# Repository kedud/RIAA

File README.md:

# RIAA

This module is a switchable RIAA/Line preamp for RM4 mixer project.

Some of the part are not present on the schematic:
 - Molex crimps

| Parts 			| 	 Part ref		|
| ----------------- | ----------------- |
| Molex crimps 		| 538-08-50-0114    |

The BoM for this schematics can be found [here](https://octopart.com/bom-tool/uFlDQjD4)

A Mouser cart is also available [here](https://www.mouser.com/ProjectManager/ProjectDetail.aspx?AccessID=9f5cd040c6)

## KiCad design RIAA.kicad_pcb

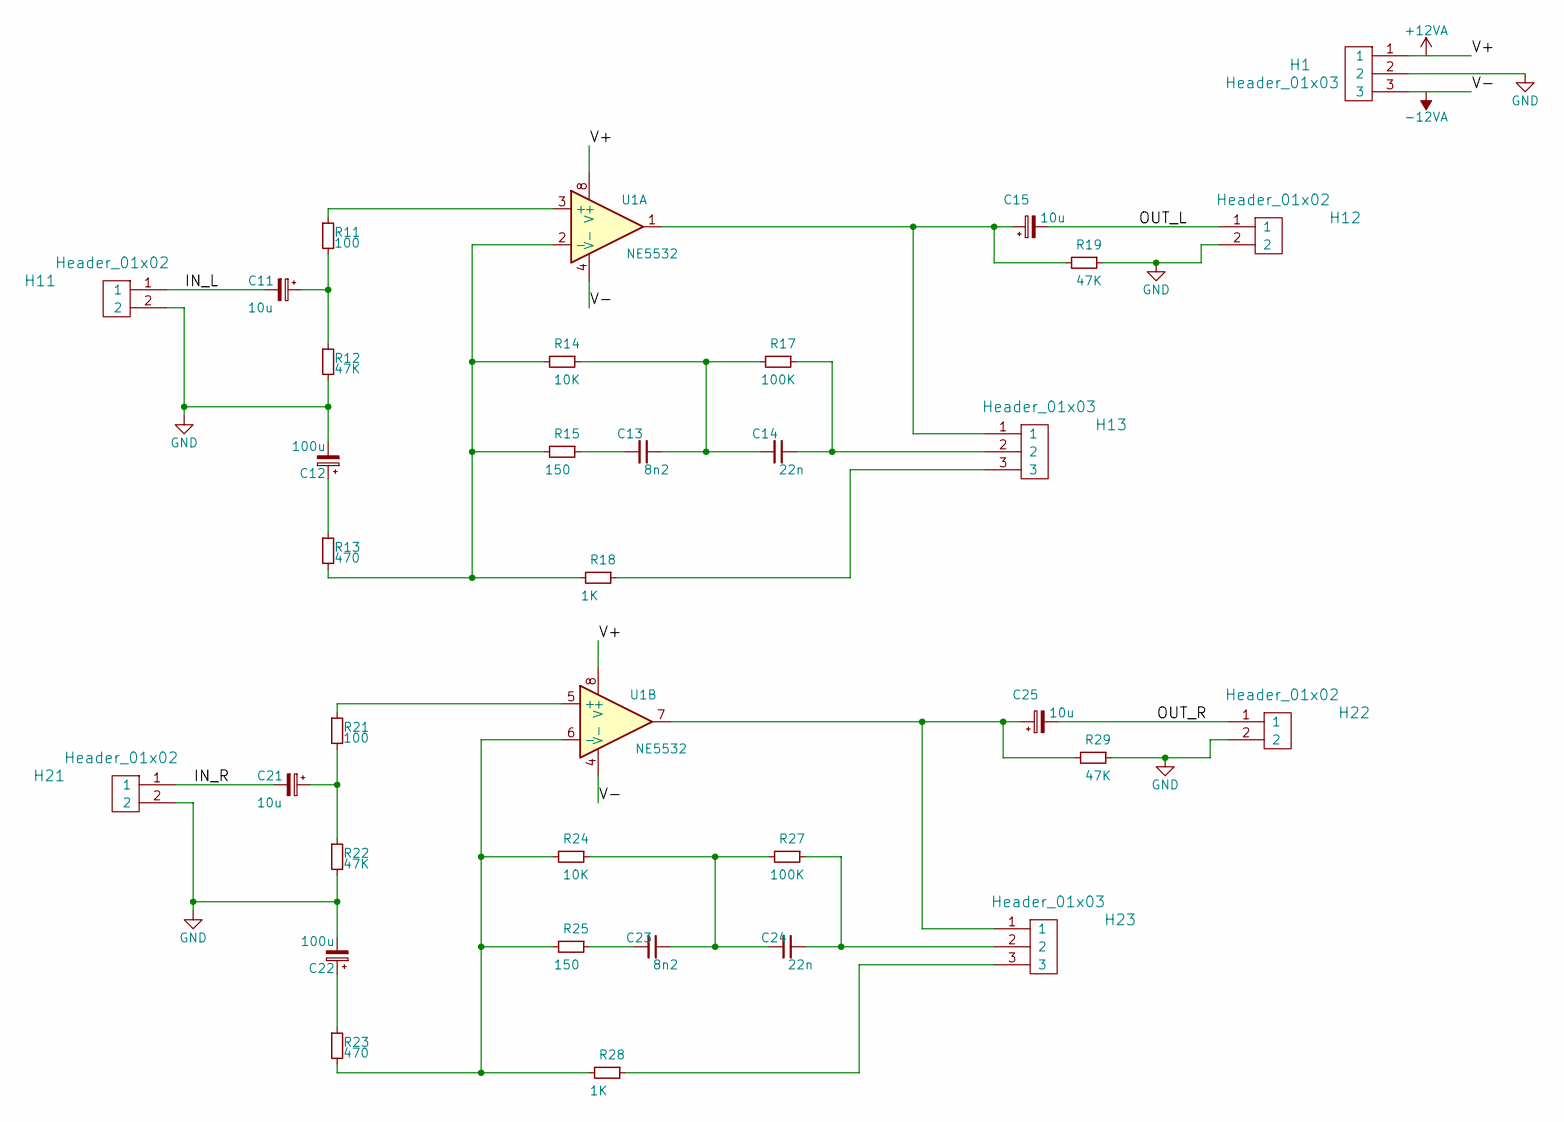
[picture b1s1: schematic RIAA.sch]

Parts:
C11, C21: 10u; C_Radial_D5_L11_P2.5; Mfg_Part_No UVR1V100MDD1TA
C12, C22: 100u; C_Radial_D5_L11_P2.5; Mfg_Part_No UVR1A101MDD
C13, C23: 8n2; C_Rect_L7_W2.5_P5; Mfg_Part_No QYX2A822KTP
C14, C24: 22n; C_Rect_L7_W2.5_P5; Mfg_Part_No QYX2A223KTP
C15, C25: 10u; C_Radial_D5_L11_P2.5; Mfg_Part_No UVR1A101MDD
H1, H13, H23: Header_01x03; Pin_Header_Straight_1x03
H11, H12, H21, H22: Header_01x02; Pin_Header_Straight_1x02
R11, R21: 100; Resistor_Horizontal_RM10mm; Mfg_Part_No CCF07100RJKE36
R12, R19, R22, R29: 47K; Resistor_Horizontal_RM10mm; Mfg_Part_No CCF0747K0GKE36
R13, R23: 470; Resistor_Horizontal_RM10mm; Mfg_Part_No CCF07470RGKE36 CCF07470RGKE36 CCF07470R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
R14, R24: 10K; Resistor_Horizontal_RM10mm; Mfg_Part_No CCF0710K0GKE36
R15, R25: 150; Resistor_Horizontal_RM10mm; Mfg_Part_No CCF07150RGKE36
R17, R27: 100K; Resistor_Horizontal_RM10mm; Mfg_Part_No CCF07100KGKE36
R18, R28: 1K; Resistor_Horizontal_RM10mm
U1: NE5532; DIP-8_W7.62mm_LongPads; Mfg_Part_No NE5532P

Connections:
/IN_L: C11.2, H11.1
/IN_R: C21.2, H21.1
/OUT_L: C15.2, H12.1
/OUT_R: C25.2, H22.1
/V+: H1.1, U1.8 (V+)
/V-: H1.3, U1.4 (V-)
GND: C12.2, C22.2, H1.2, H11.2, H12.2, H21.2, H22.2, R12.2, R19.1, R22.2, R29.1
unnamed: C11.1, R11.2, R12.1
unnamed: C12.1, R13.1
unnamed: C13.1, C14.2, R14.1, R17.2
unnamed: C13.2, R15.1
unnamed: C14.1, H13.2, R17.1
unnamed: C15.1, H13.1, R19.2, U1.1
unnamed: C21.1, R21.2, R22.1
unnamed: C22.1, R23.1
unnamed: C23.1, C24.2, R24.1, R27.2
unnamed: C23.2, R25.1
unnamed: C24.1, H23.2, R27.1
unnamed: C25.1, H23.1, R29.2, U1.7
unnamed: H13.3, R18.1
unnamed: H23.3, R28.1
unnamed: R11.1, U1.3 (+)
unnamed: R13.2, R14.2, R15.2, R18.2, U1.2 (-)
unnamed: R21.1, U1.5 (+)
unnamed: R23.2, R24.2, R25.2, R28.2, U1.6 (-)

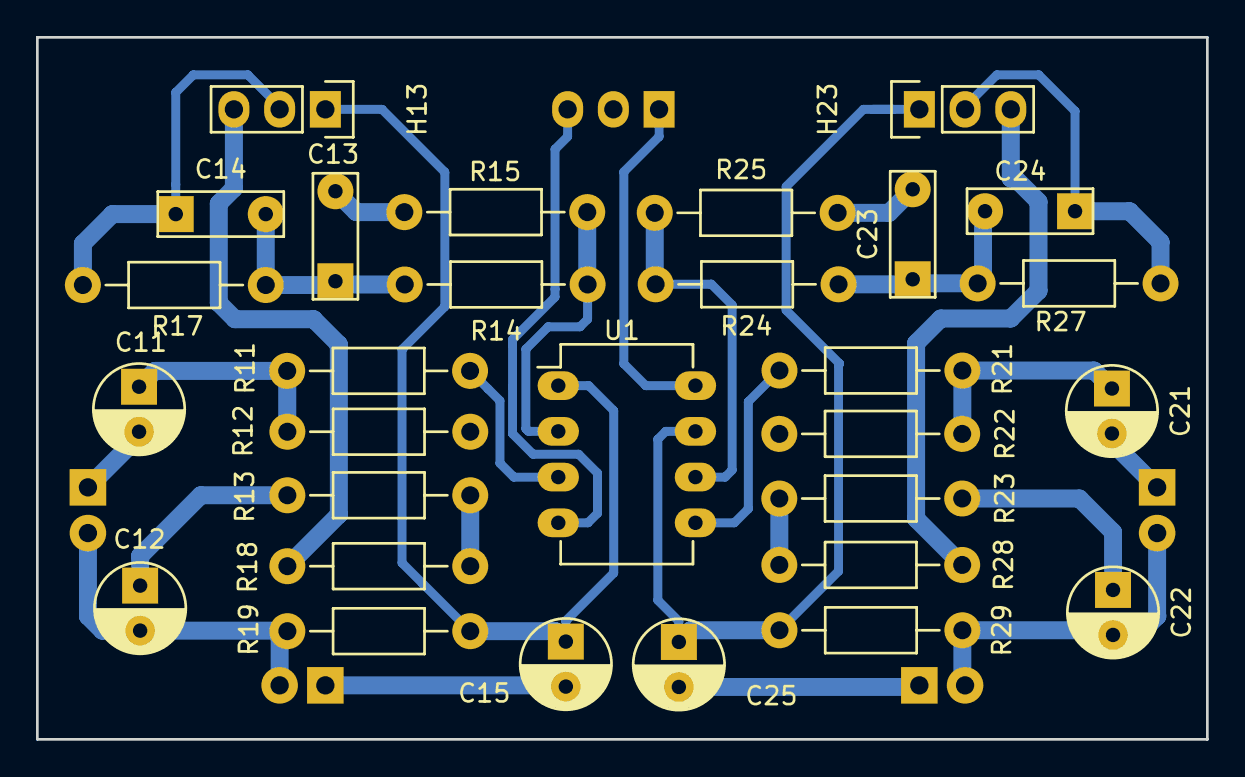
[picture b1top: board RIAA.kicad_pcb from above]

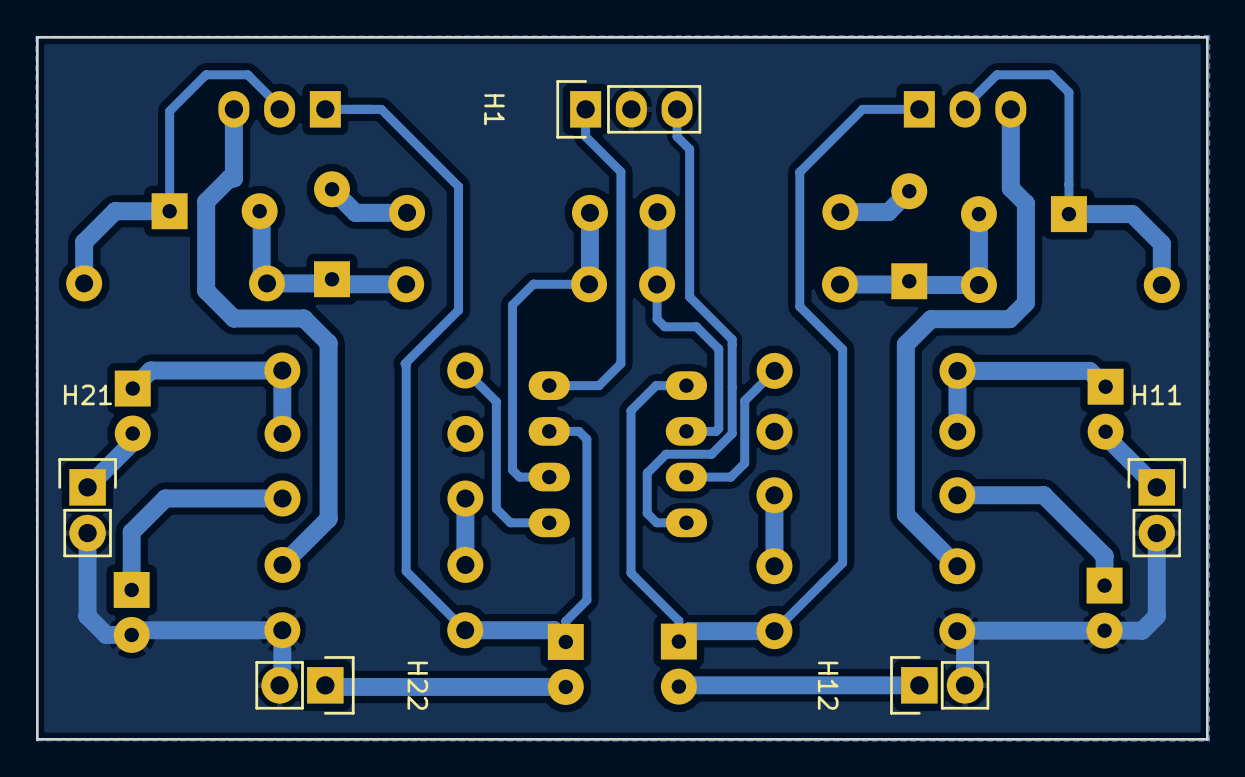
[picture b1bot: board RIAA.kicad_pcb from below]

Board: 2 copper layers, 65.0 x 39.0 mm, 34 parts (5 on the bottom side), 25 nets.

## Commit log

2017-11-17 remove unused library
2017-11-17 Partial update to add Molex connector for the switch connection
2017-11-17 Add README.md
2017-11-21 Add OpAmp references
2017-11-21 Adding switches for line/phono input commutation
2017-12-25 Updating template with correct dimensions & annotations
2017-12-25 Updating components references
2017-12-25 Updating README with Octoparts & Mouser links
